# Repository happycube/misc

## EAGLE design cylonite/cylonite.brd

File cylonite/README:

This is a board made for the EAGLE class at the SB Hackerspace.  This board will almost
certainly never be built.

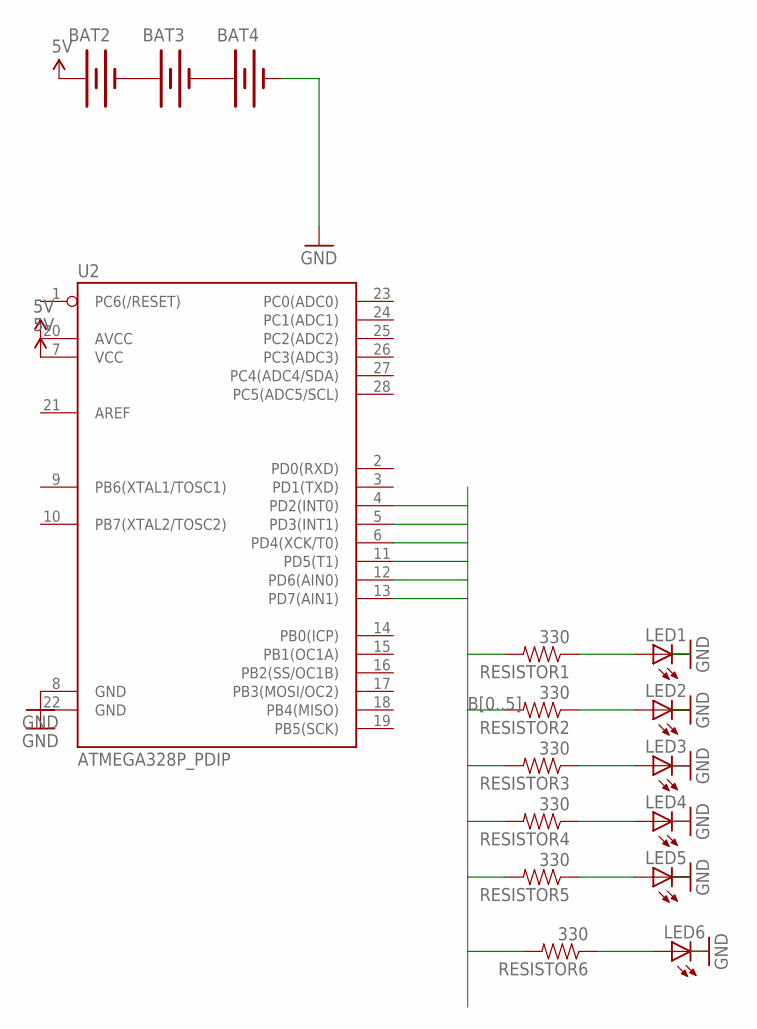
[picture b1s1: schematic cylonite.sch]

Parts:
BAT2, BAT3, BAT4: BATTERYAA; BATTERY-AA
LED1, LED2, LED3, LED4, LED5, LED6: LED5MM
RESISTOR1, RESISTOR2, RESISTOR3, RESISTOR4, RESISTOR5, RESISTOR6: 330; AXIAL-0.4
U2: ATMEGA328P_PDIP; DIL28-3

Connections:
5V: BAT2.PWR@1 (+), U2.7 (VCC), U2.20 (AVCC)
B0: RESISTOR1.P$2 (2), U2.4 (PD2(INT0))
B1: RESISTOR2.P$2 (2), U2.5 (PD3(INT1))
B2: RESISTOR3.P$2 (2), U2.6 (PD4(XCK/T0))
B3: RESISTOR4.P$2 (2), U2.11 (PD5(T1))
B4: RESISTOR5.P$2 (2), U2.12 (PD6(AIN0))
B5: RESISTOR6.P$2 (2), U2.13 (PD7(AIN1))
GND: BAT4.GND@1 (-), LED1.K (C), LED2.K (C), LED3.K (C), LED4.K (C), LED5.K (C), LED6.K (C), U2.8 (GND), U2.22 (GND)
unnamed: LED1.A, RESISTOR1.P$1 (1)
unnamed: LED2.A, RESISTOR2.P$1 (1)
unnamed: LED6.A, RESISTOR6.P$1 (1)
unnamed: BAT2.GND@1 (-), BAT3.PWR@1 (+)
unnamed: LED3.A, RESISTOR3.P$1 (1)
unnamed: BAT3.GND@1 (-), BAT4.PWR@1 (+)
unnamed: LED4.A, RESISTOR4.P$1 (1)
unnamed: LED5.A, RESISTOR5.P$1 (1)

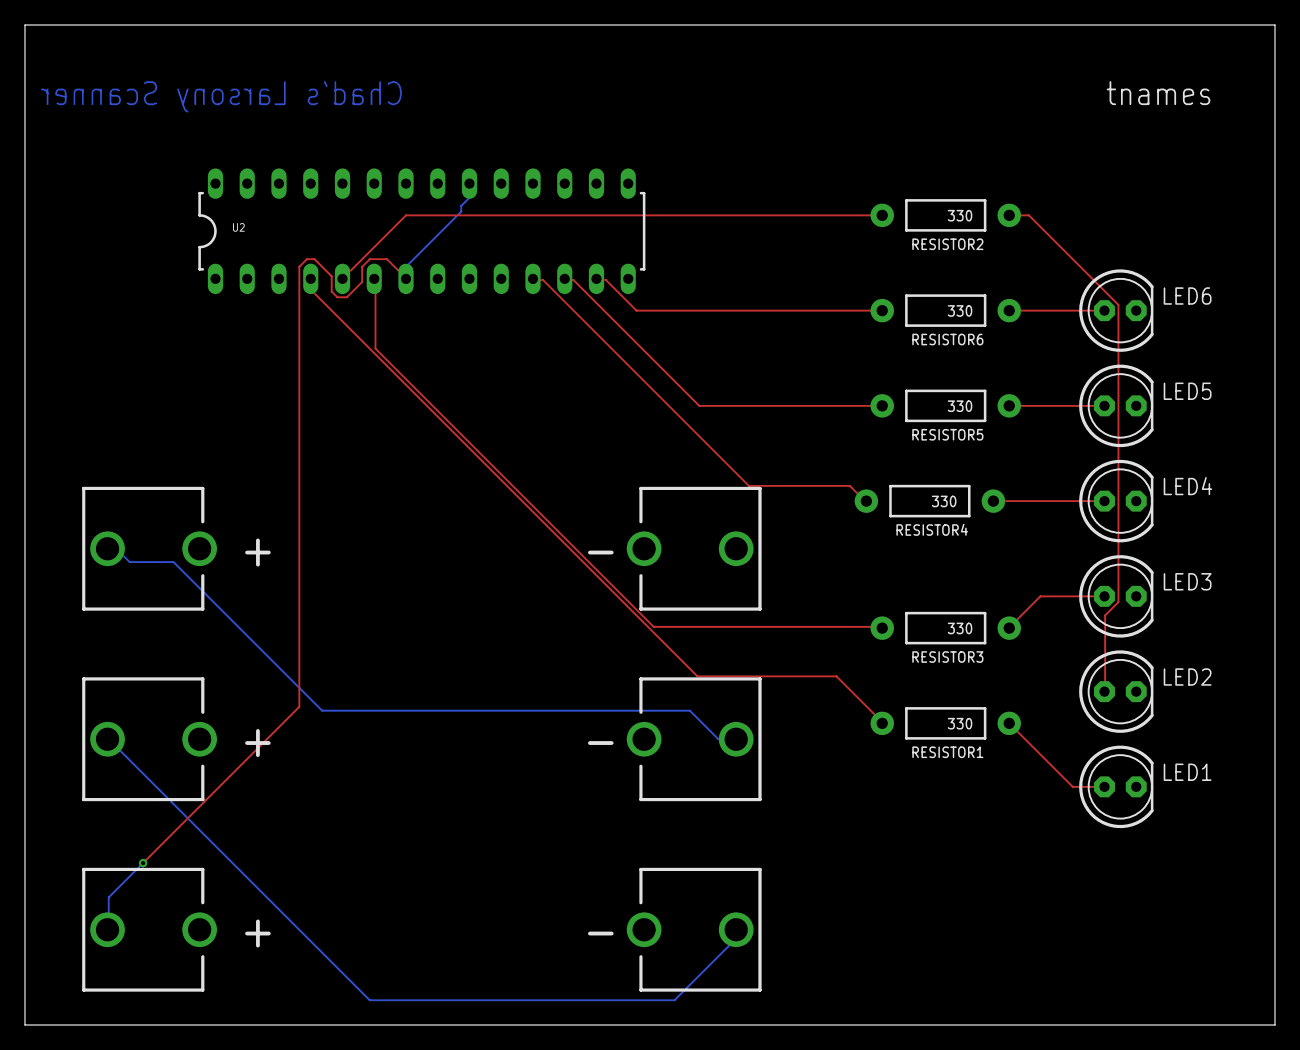
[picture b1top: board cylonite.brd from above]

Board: 2 copper layers, 100.0 x 80.0 mm, 16 parts (0 on the bottom side), 16 nets.

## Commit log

2015-01-27 design for sbhx class
2015-01-27 add silkscreen
2015-02-08 first part. still needs selection handling
2015-02-08 finished MVP version. listens on ports 4000-4015, select which one to pipe to stdout by pressing 0..9, aA..aF.
2015-02-09 fix odd # read handling
2015-02-09 add imaging stuff and support
2015-02-15 more complete readme, remove urllib need in rpi_stream, try to clean up sockets better
2015-02-15 now use integrated opencv image displayer
2015-02-15 removed "updated" debug print and reduced waitKey to 1ms
2015-02-16 added reuseaddr to allow quicker restarts
2015-02-16 fix up readme and clear screen as needed
2015-02-18 add -DSHOWALL to view all windows at once
2015-02-18 only do one waitKey per display
2015-02-18 implemented command line options - '-a' to show all screens, '-s' to save audio (raw 16-bit samples)
2015-02-28 bug fixes from dburr
2015-02-28 remove non-mmap methods
2015-03-09 WIP: multi-camera capturer conversion

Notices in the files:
parts and their libraries:
SparkFun-Electromechanical: Licensing: Creative Commons ShareAlike 4.0 International - https://creativecommons.org/licenses/by-sa/4.0
